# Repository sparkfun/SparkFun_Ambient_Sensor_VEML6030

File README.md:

SparkFun Ambient Light Sensor VEML6030 (Qwiic) 
========================================

[*SparkFun Ambient LIght Sensor - VEML6030 (Qwiic) (SEN-15436)*](https://www.sparkfun.com/products/15436)

The SparkFun Ambient Light Sensor - VEML6030 (Qwiic) is an I<sup>2</sup>C enabled
ambient light sensor with high sensitivity and high accuracy. It reads ambient
light in Lux and boasts a number of nice features including: the ability to set
high and low thresholds for an optional interrupt, power saving features that enable
single digit micro-amp current draw, and a readable  range from zero to 120,000 Lux. We've also written an Arduino 
library that gives full access to all features and includes example code demonstrating all its' abilities (see link below under **Documentation**). 

Repository Contents
-------------------

* **/Documentation** - Data sheets, additional product information
* **/Hardware** - Eagle design files (.brd, .sch)
* **/Libraries** - Libraries for use with the SparkFun Ambient Light Sensor.
* **/Production** - Production panel files (.brd)

Documentation
--------------
* **[SparkFun Ambient Light Sensor Arduino Library](https://github.com/sparkfun/SparkFun_Ambient_Light_Sensor_Arduino_Library)** - Arduino Library
* **[Hookup Guide](https://learn.sparkfun.com/tutorials/qwiic-ambient-light-sensor-veml6030-hookup-guide)** - Basic hookup guide for the SparkFun Ambient Light Sensor
* **[Qwiic Ecosystem](https://www.sparkfun.com/qwiic)** - Qwiic enabled for fast prototyping!

License Information
-------------------

This product is _**open source**_! 

Please review the LICENSE.md file for license information. 

If you have any questions or concerns on licensing, please contact technical support on our [SparkFun forums](https://forum.sparkfun.com/viewforum.php?f=152).

Distributed as-is; no warranty is given.

- Your friends at SparkFun.

_<COLLABORATION CREDIT>_

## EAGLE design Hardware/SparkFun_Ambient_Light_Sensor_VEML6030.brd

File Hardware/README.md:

SparkFun Ambient Light Sensor VEML6030 Design Files
=====================================

The .sch and .brd files hare are Eagle CAD schematic and PCB design files from SparkFun Electronics.
A freeware version of Eagle can be found [here](http://www.cadsoftusa.com/download-eagle/freeware/).

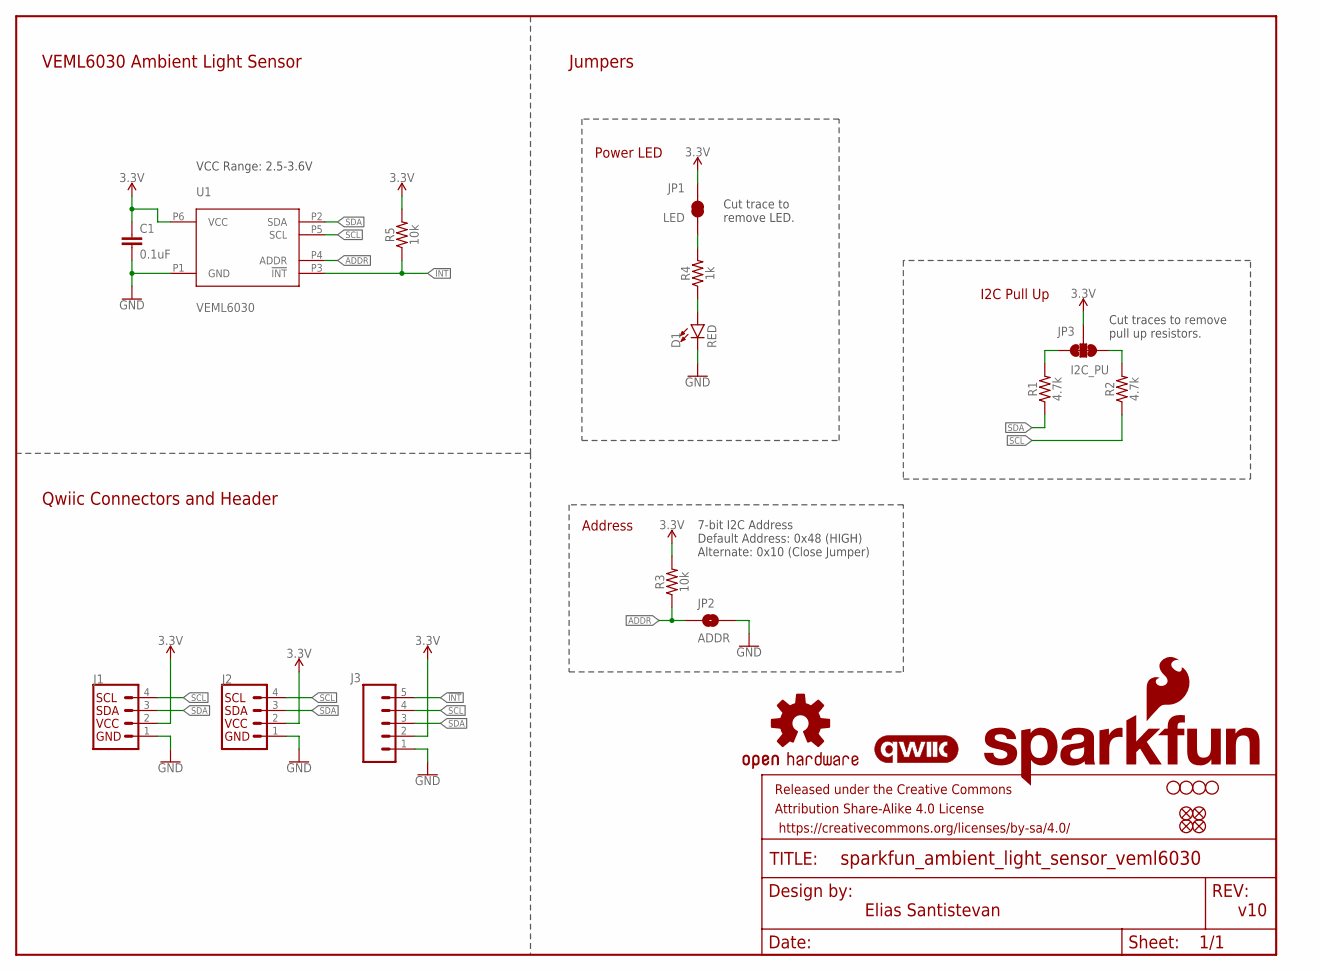
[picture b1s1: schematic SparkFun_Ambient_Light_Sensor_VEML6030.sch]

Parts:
C1: 0.1uF; 0603
D1: RED; LED-0603
FD1, FD2, FD3, FD4: FIDUCIAL1X2; FIDUCIAL-1X2
FRAME1: FRAME-LETTER; CREATIVE_COMMONS
H1, H2, H3, H4: STAND-OFFTIGHT; STAND-OFF-TIGHT
J1, J2: QWIIC_CONNECTORJS-1MM; JST04_1MM_RA
J3: CONN_05NO_SILK; 1X05_NO_SILK
JP1: LED; SMT-JUMPER_2_NC_TRACE_SILK
JP2: ADDR; SMT-JUMPER_2_NO_SILK
JP3: I2C_PU; SMT-JUMPER_3_2-NC_TRACE_SILK
LOGO1: SFE_LOGO_NAME_FLAME.1_INCH; SFE_LOGO_NAME_FLAME_.1
LOGO2: OSHW-LOGOS; OSHW-LOGO-S
R1, R2: 4.7k; 0603
R3, R5: 10k; 0603
R4: 1k; 0603
U1: VEML6030
U$1: QWIIC_LOGO_5MM; QWIIC_5MM

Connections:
3.3V: C1.1, J1.2, J2.2, J3.2, JP1.2, JP3.2, R3.2, R5.2, U1.P6 (VCC)
!INT: J3.5, R5.1, U1.P3 (!INT)
ADDR: JP2.1, R3.1, U1.P4 (ADDR)
GND: C1.2, D1.C, J1.1, J2.1, J3.1, JP2.2, U1.P1 (GND)
unnamed: D1.A, R4.1
unnamed: JP1.1, R4.2
unnamed: JP3.3, R1.2
unnamed: JP3.1, R2.2
SCL: J1.4, J2.4, J3.4, R2.1, U1.P5 (SCL)
SDA: J1.3, J2.3, J3.3, R1.1, U1.P2 (SDA)

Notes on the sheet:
v10
Elias Santistevan
Qwiic Connectors and Header
VEML6030 Ambient Light Sensor
Jumpers
Power LED
I2C Pull Up
Address
7-bit I2C Address Default Address: 0x48 (HIGH) Alternate: 0x10 (Close Jumper)
Cut trace to remove LED.
Cut traces to remove pull up resistors.
VCC Range: 2.5-3.6V

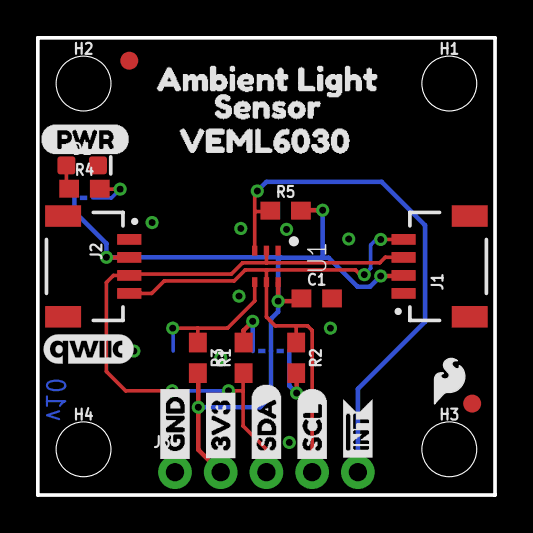
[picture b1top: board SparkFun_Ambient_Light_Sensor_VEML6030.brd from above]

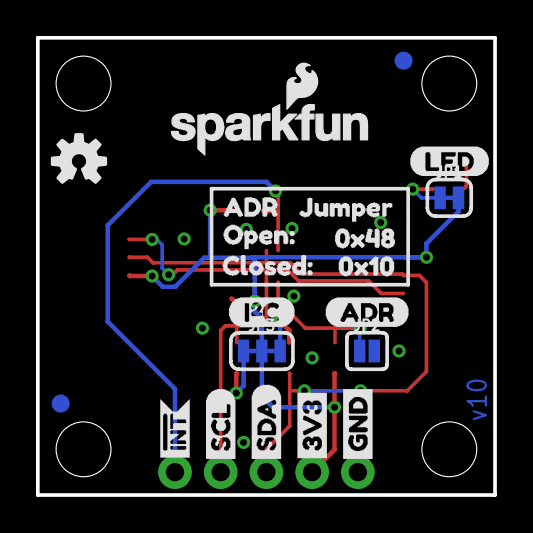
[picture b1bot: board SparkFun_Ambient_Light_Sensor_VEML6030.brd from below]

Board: 2 copper layers, 25.4 x 25.4 mm, 50 parts (21 on the bottom side), 10 nets.

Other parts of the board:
U$2, U$11: 3V3-04
U$3, U$8: GND-04
U$4, U$9: SDA-[)
U$5, U$10: SCL-[)
U$6, U$7: INT#-[<
U$12: I_SUPER2_C-()-04
U$13: ADR-()
U$14: LED0
U$15: AMBIENT_LIGHT0
U$16: SENSOR1
U$17: VEML60302
U$18: SFE_LOGO_FLAME_.1
U$19: PWR-()-04
U$20: CLOSED#2
U$21: OPEN#0
U$22: 0X481
U$24: 0X103
U$25: ADR0
U$26: JUMPER1

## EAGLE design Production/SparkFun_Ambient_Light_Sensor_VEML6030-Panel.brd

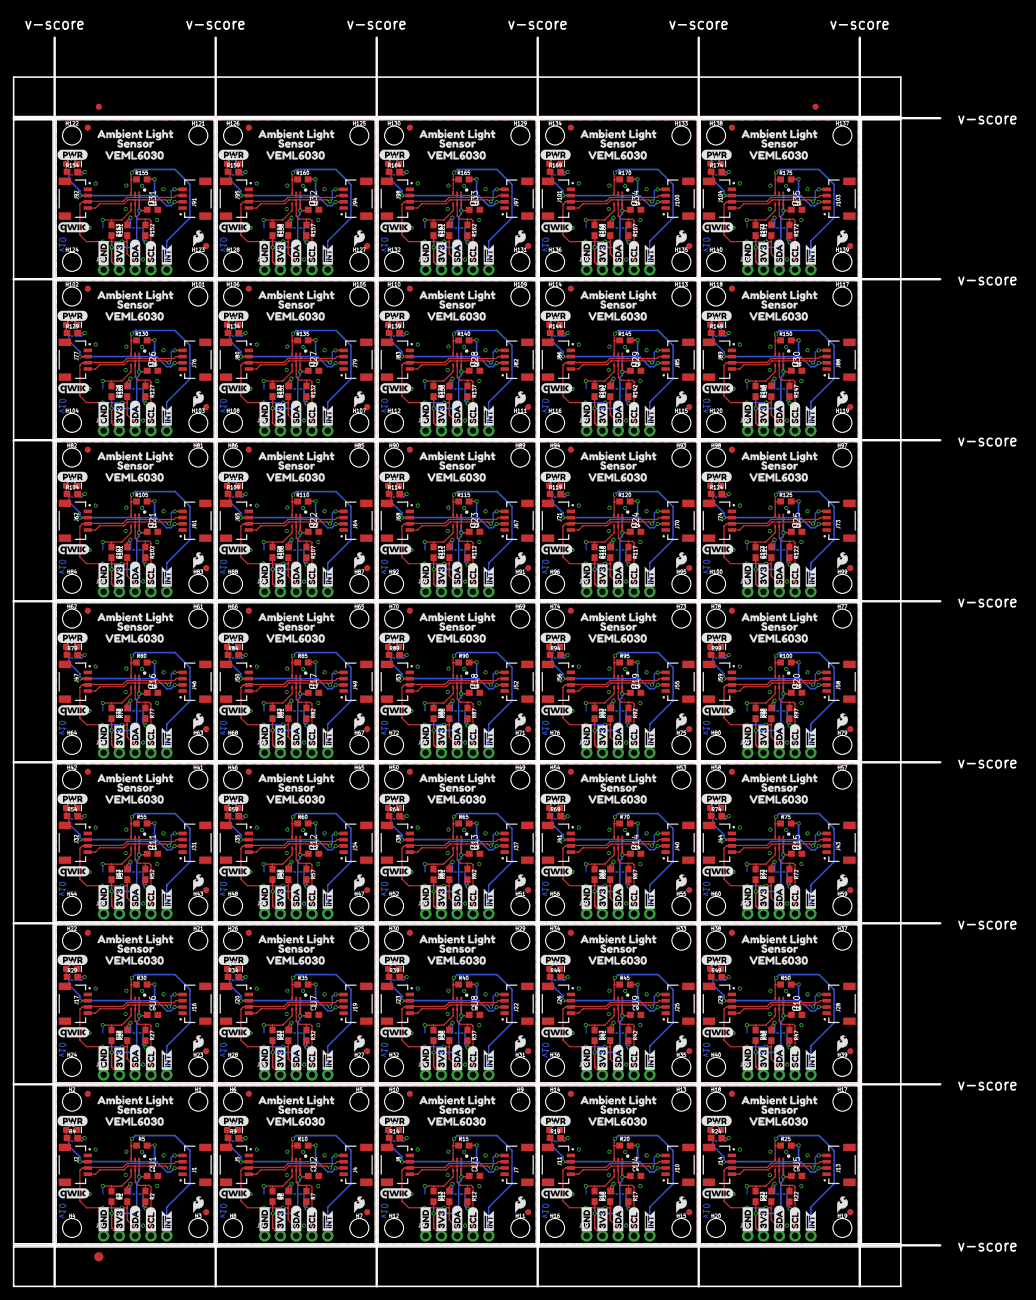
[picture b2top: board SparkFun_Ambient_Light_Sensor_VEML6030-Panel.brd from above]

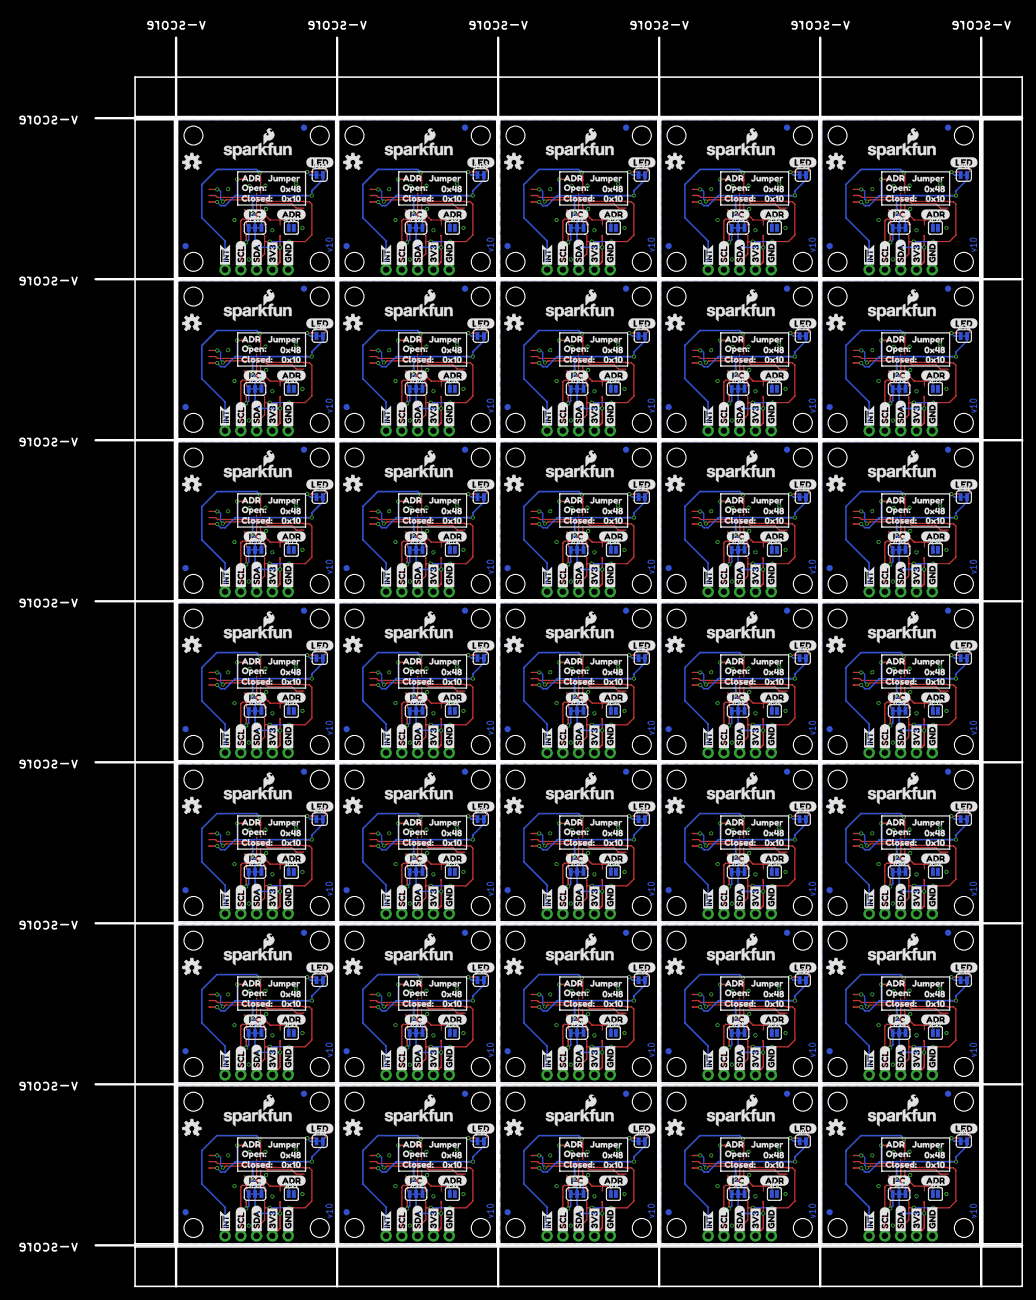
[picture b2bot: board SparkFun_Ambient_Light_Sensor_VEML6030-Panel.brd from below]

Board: 2 copper layers, 149.1 x 200.9 mm, 1718 parts (735 on the bottom side), 350 nets.

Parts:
C1, C2, C3, C4, C5, C6, C7, C8, C9, C10, C11, C12, C13, C14, C15, C16, C17, C18, C19, C20, C21, C22, C23, C24, C25, C26, C27, C28, C29, C30, C31, C32, C33, C34, C35: 0.1uF; 0603
D1, D2, D3, D4, D5, D6, D7, D8, D9, D10, D11, D12, D13, D14, D15, D16, D17, D18, D19, D20, D21, D22, D23, D24, D25, D26, D27, D28, D29, D30, D31, D32, D33, D34, D35: RED; LED-0603
E$1, E$2: FIDUCIAL-1X2
E$3: FIDUCIAL-1.5X3
FD1, FD2, FD3, FD4, FD5, FD6, FD7, FD8, FD9, FD10, FD11, FD12, FD13, FD14, FD15, FD16, FD17, FD18, FD19, FD20, FD21, FD22, FD23, FD24, FD25, FD26, FD27, FD28, FD29, FD30, FD31, FD32, FD33, FD34, FD35, FD36, FD37, FD38, FD39, FD40, FD41, FD42, FD43, FD44, FD45, FD46, FD47, FD48, FD49, FD50, FD51, FD52, FD53, FD54, FD55, FD56, FD57, FD58, FD59, FD60, FD61, FD62, FD63, FD64, FD65, FD66, FD67, FD68, FD69, FD70, FD71, FD72, FD73, FD74, FD75, FD76, FD77, FD78, FD79, FD80, FD81, FD82, FD83, FD84, FD85, FD86, FD87, FD88, FD89, FD90, FD91, FD92, FD93, FD94, FD95, FD96, FD97, FD98, FD99, FD100, FD101, FD102, FD103, FD104, FD105, FD106, FD107, FD108, FD109, FD110, FD111, FD112, FD113, FD114, FD115, FD116, FD117, FD118, FD119, FD120, FD121, FD122, FD123, FD124, FD125, FD126, FD127, FD128, FD129, FD130, FD131, FD132, FD133, FD134, FD135, FD136, FD137, FD138, FD139, FD140: FIDUCIAL1X2; FIDUCIAL-1X2
H1, H2, H3, H4, H5, H6, H7, H8, H9, H10, H11, H12, H13, H14, H15, H16, H17, H18, H19, H20, H21, H22, H23, H24, H25, H26, H27, H28, H29, H30, H31, H32, H33, H34, H35, H36, H37, H38, H39, H40, H41, H42, H43, H44, H45, H46, H47, H48, H49, H50, H51, H52, H53, H54, H55, H56, H57, H58, H59, H60, H61, H62, H63, H64, H65, H66, H67, H68, H69, H70, H71, H72, H73, H74, H75, H76, H77, H78, H79, H80, H81, H82, H83, H84, H85, H86, H87, H88, H89, H90, H91, H92, H93, H94, H95, H96, H97, H98, H99, H100, H101, H102, H103, H104, H105, H106, H107, H108, H109, H110, H111, H112, H113, H114, H115, H116, H117, H118, H119, H120, H121, H122, H123, H124, H125, H126, H127, H128, H129, H130, H131, H132, H133, H134, H135, H136, H137, H138, H139, H140: STAND-OFFTIGHT; STAND-OFF-TIGHT
J1, J2, J4, J5, J7, J8, J10, J11, J13, J14, J16, J17, J19, J20, J22, J23, J25, J26, J28, J29, J31, J32, J34, J35, J37, J38, J40, J41, J43, J44, J46, J47, J49, J50, J52, J53, J55, J56, J58, J59, J61, J62, J64, J65, J67, J68, J70, J71, J73, J74, J76, J77, J79, J80, J82, J83, J85, J86, J88, J89, J91, J92, J94, J95, J97, J98, J100, J101, J103, J104: JST04_1MM_RA
J3, J6, J9, J12, J15, J18, J21, J24, J27, J30, J33, J36, J39, J42, J45, J48, J51, J54, J57, J60, J63, J66, J69, J72, J75, J78, J81, J84, J87, J90, J93, J96, J99, J102, J105: 1X05_NO_SILK
JP1, JP4, JP7, JP10, JP13, JP16, JP19, JP22, JP25, JP28, JP31, JP34, JP37, JP40, JP43, JP46, JP49, JP52, JP55, JP58, JP61, JP64, JP67, JP70, JP73, JP76, JP79, JP82, JP85, JP88, JP91, JP94, JP97, JP100, JP103: LED; SMT-JUMPER_2_NC_TRACE_SILK
JP2, JP5, JP8, JP11, JP14, JP17, JP20, JP23, JP26, JP29, JP32, JP35, JP38, JP41, JP44, JP47, JP50, JP53, JP56, JP59, JP62, JP65, JP68, JP71, JP74, JP77, JP80, JP83, JP86, JP89, JP92, JP95, JP98, JP101, JP104: ADDR; SMT-JUMPER_2_NO_SILK
JP3, JP6, JP9, JP12, JP15, JP18, JP21, JP24, JP27, JP30, JP33, JP36, JP39, JP42, JP45, JP48, JP51, JP54, JP57, JP60, JP63, JP66, JP69, JP72, JP75, JP78, JP81, JP84, JP87, JP90, JP93, JP96, JP99, JP102, JP105: I2C_PU; SMT-JUMPER_3_2-NC_TRACE_SILK
LOGO1, LOGO3, LOGO5, LOGO7, LOGO9, LOGO11, LOGO13, LOGO15, LOGO17, LOGO19, LOGO21, LOGO23, LOGO25, LOGO27, LOGO29, LOGO31, LOGO33, LOGO35, LOGO37, LOGO39, LOGO41, LOGO43, LOGO45, LOGO47, LOGO49, LOGO51, LOGO53, LOGO55, LOGO57, LOGO59, LOGO61, LOGO63, LOGO65, LOGO67, LOGO69: SFE_LOGO_NAME_FLAME.1_INCH; SFE_LOGO_NAME_FLAME_.1
LOGO2, LOGO4, LOGO6, LOGO8, LOGO10, LOGO12, LOGO14, LOGO16, LOGO18, LOGO20, LOGO22, LOGO24, LOGO26, LOGO28, LOGO30, LOGO32, LOGO34, LOGO36, LOGO38, LOGO40, LOGO42, LOGO44, LOGO46, LOGO48, LOGO50, LOGO52, LOGO54, LOGO56, LOGO58, LOGO60, LOGO62, LOGO64, LOGO66, LOGO68, LOGO70: OSHW-LOGOS; OSHW-LOGO-S
R1, R2, R6, R7, R11, R12, R16, R17, R21, R22, R26, R27, R31, R32, R36, R37, R41, R42, R46, R47, R51, R52, R56, R57, R61, R62, R66, R67, R71, R72, R76, R77, R81, R82, R86, R87, R91, R92, R96, R97, R101, R102, R106, R107, R111, R112, R116, R117, R121, R122, R126, R127, R131, R132, R136, R137, R141, R142, R146, R147, R151, R152, R156, R157, R161, R162, R166, R167, R171, R172: 4.7k; 0603
R3, R5, R8, R10, R13, R15, R18, R20, R23, R25, R28, R30, R33, R35, R38, R40, R43, R45, R48, R50, R53, R55, R58, R60, R63, R65, R68, R70, R73, R75, R78, R80, R83, R85, R88, R90, R93, R95, R98, R100, R103, R105, R108, R110, R113, R115, R118, R120, R123, R125, R128, R130, R133, R135, R138, R140, R143, R145, R148, R150, R153, R155, R158, R160, R163, R165, R168, R170, R173, R175: 10k; 0603
R4, R9, R14, R19, R24, R29, R34, R39, R44, R49, R54, R59, R64, R69, R74, R79, R84, R89, R94, R99, R104, R109, R114, R119, R124, R129, R134, R139, R144, R149, R154, R159, R164, R169, R174: 1k; 0603
U1, U2, U3, U4, U5, U6, U7, U8, U9, U10, U11, U12, U13, U14, U15, U16, U17, U18, U19, U20, U21, U22, U23, U24, U25, U26, U27, U28, U29, U30, U31, U32, U33, U34, U35: VEML6030
U$1, U$23, U$51, U$76, U$101, U$126, U$151, U$176, U$201, U$226, U$251, U$276, U$301, U$326, U$351, U$376, U$401, U$426, U$451, U$476, U$501, U$526, U$551, U$576, U$601, U$626, U$651, U$676, U$701, U$726, U$751, U$776, U$801, U$826, U$851: QWIIC_LOGO_5MM; QWIIC_5MM
U$2, U$11, U$27, U$36, U$52, U$61, U$77, U$86, U$102, U$111, U$127, U$136, U$152, U$161, U$177, U$186, U$202, U$211, U$227, U$236, U$252, U$261, U$277, U$286, U$302, U$311, U$327, U$336, U$352, U$361, U$377, U$386, U$402, U$411, U$427, U$436, U$452, U$461, U$477, U$486, U$502, U$511, U$527, U$536, U$552, U$561, U$577, U$586, U$602, U$611, U$627, U$636, U$652, U$661, U$677, U$686, U$702, U$711, U$727, U$736, U$752, U$761, U$777, U$786, U$802, U$811, U$827, U$836, U$852, U$861: 3V3-04
U$3, U$8, U$28, U$33, U$53, U$58, U$78, U$83, U$103, U$108, U$128, U$133, U$153, U$158, U$178, U$183, U$203, U$208, U$228, U$233, U$253, U$258, U$278, U$283, U$303, U$308, U$328, U$333, U$353, U$358, U$378, U$383, U$403, U$408, U$428, U$433, U$453, U$458, U$478, U$483, U$503, U$508, U$528, U$533, U$553, U$558, U$578, U$583, U$603, U$608, U$628, U$633, U$653, U$658, U$678, U$683, U$703, U$708, U$728, U$733, U$753, U$758, U$778, U$783, U$803, U$808, U$828, U$833, U$853, U$858: GND-04
U$4, U$9, U$29, U$34, U$54, U$59, U$79, U$84, U$104, U$109, U$129, U$134, U$154, U$159, U$179, U$184, U$204, U$209, U$229, U$234, U$254, U$259, U$279, U$284, U$304, U$309, U$329, U$334, U$354, U$359, U$379, U$384, U$404, U$409, U$429, U$434, U$454, U$459, U$479, U$484, U$504, U$509, U$529, U$534, U$554, U$559, U$579, U$584, U$604, U$609, U$629, U$634, U$654, U$659, U$679, U$684, U$704, U$709, U$729, U$734, U$754, U$759, U$779, U$784, U$804, U$809, U$829, U$834, U$854, U$859: SDA-[)
U$5, U$10, U$30, U$35, U$55, U$60, U$80, U$85, U$105, U$110, U$130, U$135, U$155, U$160, U$180, U$185, U$205, U$210, U$230, U$235, U$255, U$260, U$280, U$285, U$305, U$310, U$330, U$335, U$355, U$360, U$380, U$385, U$405, U$410, U$430, U$435, U$455, U$460, U$480, U$485, U$505, U$510, U$530, U$535, U$555, U$560, U$580, U$585, U$605, U$610, U$630, U$635, U$655, U$660, U$680, U$685, U$705, U$710, U$730, U$735, U$755, U$760, U$780, U$785, U$805, U$810, U$830, U$835, U$855, U$860: SCL-[)
U$6, U$7, U$31, U$32, U$56, U$57, U$81, U$82, U$106, U$107, U$131, U$132, U$156, U$157, U$181, U$182, U$206, U$207, U$231, U$232, U$256, U$257, U$281, U$282, U$306, U$307, U$331, U$332, U$356, U$357, U$381, U$382, U$406, U$407, U$431, U$432, U$456, U$457, U$481, U$482, U$506, U$507, U$531, U$532, U$556, U$557, U$581, U$582, U$606, U$607, U$631, U$632, U$656, U$657, U$681, U$682, U$706, U$707, U$731, U$732, U$756, U$757, U$781, U$782, U$806, U$807, U$831, U$832, U$856, U$857: INT#-[<
U$12, U$37, U$62, U$87, U$112, U$137, U$162, U$187, U$212, U$237, U$262, U$287, U$312, U$337, U$362, U$387, U$412, U$437, U$462, U$487, U$512, U$537, U$562, U$587, U$612, U$637, U$662, U$687, U$712, U$737, U$762, U$787, U$812, U$837, U$862: I_SUPER2_C-()-04
U$13, U$38, U$63, U$88, U$113, U$138, U$163, U$188, U$213, U$238, U$263, U$288, U$313, U$338, U$363, U$388, U$413, U$438, U$463, U$488, U$513, U$538, U$563, U$588, U$613, U$638, U$663, U$688, U$713, U$738, U$763, U$788, U$813, U$838, U$863: ADR-()
U$14, U$39, U$64, U$89, U$114, U$139, U$164, U$189, U$214, U$239, U$264, U$289, U$314, U$339, U$364, U$389, U$414, U$439, U$464, U$489, U$514, U$539, U$564, U$589, U$614, U$639, U$664, U$689, U$714, U$739, U$764, U$789, U$814, U$839, U$864: LED0
U$15, U$40, U$65, U$90, U$115, U$140, U$165, U$190, U$215, U$240, U$265, U$290, U$315, U$340, U$365, U$390, U$415, U$440, U$465, U$490, U$515, U$540, U$565, U$590, U$615, U$640, U$665, U$690, U$715, U$740, U$765, U$790, U$815, U$840, U$865: AMBIENT_LIGHT0
U$16, U$41, U$66, U$91, U$116, U$141, U$166, U$191, U$216, U$241, U$266, U$291, U$316, U$341, U$366, U$391, U$416, U$441, U$466, U$491, U$516, U$541, U$566, U$591, U$616, U$641, U$666, U$691, U$716, U$741, U$766, U$791, U$816, U$841, U$866: SENSOR1
U$17, U$42, U$67, U$92, U$117, U$142, U$167, U$192, U$217, U$242, U$267, U$292, U$317, U$342, U$367, U$392, U$417, U$442, U$467, U$492, U$517, U$542, U$567, U$592, U$617, U$642, U$667, U$692, U$717, U$742, U$767, U$792, U$817, U$842, U$867: VEML60302
U$18, U$43, U$68, U$93, U$118, U$143, U$168, U$193, U$218, U$243, U$268, U$293, U$318, U$343, U$368, U$393, U$418, U$443, U$468, U$493, U$518, U$543, U$568, U$593, U$618, U$643, U$668, U$693, U$718, U$743, U$768, U$793, U$818, U$843, U$868: SFE_LOGO_FLAME_.1
U$19, U$44, U$69, U$94, U$119, U$144, U$169, U$194, U$219, U$244, U$269, U$294, U$319, U$344, U$369, U$394, U$419, U$444, U$469, U$494, U$519, U$544, U$569, U$594, U$619, U$644, U$669, U$694, U$719, U$744, U$769, U$794, U$819, U$844, U$869: PWR-()-04
U$20, U$49, U$74, U$99, U$124, U$149, U$174, U$199, U$224, U$249, U$274, U$299, U$324, U$349, U$374, U$399, U$424, U$449, U$474, U$499, U$524, U$549, U$574, U$599, U$624, U$649, U$674, U$699, U$724, U$749, U$774, U$799, U$824, U$849, U$874: CLOSED#2
U$21, U$50, U$75, U$100, U$125, U$150, U$175, U$200, U$225, U$250, U$275, U$300, U$325, U$350, U$375, U$400, U$425, U$450, U$475, U$500, U$525, U$550, U$575, U$600, U$625, U$650, U$675, U$700, U$725, U$750, U$775, U$800, U$825, U$850, U$875: OPEN#0
U$22, U$45, U$70, U$95, U$120, U$145, U$170, U$195, U$220, U$245, U$270, U$295, U$320, U$345, U$370, U$395, U$420, U$445, U$470, U$495, U$520, U$545, U$570, U$595, U$620, U$645, U$670, U$695, U$720, U$745, U$770, U$795, U$820, U$845, U$870: 0X481
U$24, U$46, U$71, U$96, U$121, U$146, U$171, U$196, U$221, U$246, U$271, U$296, U$321, U$346, U$371, U$396, U$421, U$446, U$471, U$496, U$521, U$546, U$571, U$596, U$621, U$646, U$671, U$696, U$721, U$746, U$771, U$796, U$821, U$846, U$871: 0X103
U$25, U$47, U$72, U$97, U$122, U$147, U$172, U$197, U$222, U$247, U$272, U$297, U$322, U$347, U$372, U$397, U$422, U$447, U$472, U$497, U$522, U$547, U$572, U$597, U$622, U$647, U$672, U$697, U$722, U$747, U$772, U$797, U$822, U$847, U$872: ADR0
U$26, U$48, U$73, U$98, U$123, U$148, U$173, U$198, U$223, U$248, U$273, U$298, U$323, U$348, U$373, U$398, U$423, U$448, U$473, U$498, U$523, U$548, U$573, U$598, U$623, U$648, U$673, U$698, U$723, U$748, U$773, U$798, U$823, U$848, U$873: JUMPER1

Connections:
3.3V: C1.1, J1.2, J2.2, J3.2, JP1.2, JP3.2, R3.2, R5.2, U1.P6
3.3V1: C2.1, J4.2, J5.2, J6.2, JP4.2, JP6.2, R8.2, R10.2, U2.P6
3.3V2: C3.1, J7.2, J8.2, J9.2, JP7.2, JP9.2, R13.2, R15.2, U3.P6
3.3V3: C4.1, J10.2, J11.2, J12.2, JP10.2, JP12.2, R18.2, R20.2, U4.P6
3.3V4: C5.1, J13.2, J14.2, J15.2, JP13.2, JP15.2, R23.2, R25.2, U5.P6
3.3V5: C6.1, J16.2, J17.2, J18.2, JP16.2, JP18.2, R28.2, R30.2, U6.P6
3.3V6: C7.1, J19.2, J20.2, J21.2, JP19.2, JP21.2, R33.2, R35.2, U7.P6
3.3V7: C8.1, J22.2, J23.2, J24.2, JP22.2, JP24.2, R38.2, R40.2, U8.P6
3.3V8: C9.1, J25.2, J26.2, J27.2, JP25.2, JP27.2, R43.2, R45.2, U9.P6
3.3V9: C10.1, J28.2, J29.2, J30.2, JP28.2, JP30.2, R48.2, R50.2, U10.P6
3.3V10: C11.1, J31.2, J32.2, J33.2, JP31.2, JP33.2, R53.2, R55.2, U11.P6
3.3V11: C12.1, J34.2, J35.2, J36.2, JP34.2, JP36.2, R58.2, R60.2, U12.P6
3.3V12: C13.1, J37.2, J38.2, J39.2, JP37.2, JP39.2, R63.2, R65.2, U13.P6
3.3V13: C14.1, J40.2, J41.2, J42.2, JP40.2, JP42.2, R68.2, R70.2, U14.P6
3.3V14: C15.1, J43.2, J44.2, J45.2, JP43.2, JP45.2, R73.2, R75.2, U15.P6
3.3V15: C16.1, J46.2, J47.2, J48.2, JP46.2, JP48.2, R78.2, R80.2, U16.P6
3.3V16: C17.1, J49.2, J50.2, J51.2, JP49.2, JP51.2, R83.2, R85.2, U17.P6
3.3V17: C18.1, J52.2, J53.2, J54.2, JP52.2, JP54.2, R88.2, R90.2, U18.P6
3.3V18: C19.1, J55.2, J56.2, J57.2, JP55.2, JP57.2, R93.2, R95.2, U19.P6
3.3V19: C20.1, J58.2, J59.2, J60.2, JP58.2, JP60.2, R98.2, R100.2, U20.P6
3.3V20: C21.1, J61.2, J62.2, J63.2, JP61.2, JP63.2, R103.2, R105.2, U21.P6
3.3V21: C22.1, J64.2, J65.2, J66.2, JP64.2, JP66.2, R108.2, R110.2, U22.P6
3.3V22: C23.1, J67.2, J68.2, J69.2, JP67.2, JP69.2, R113.2, R115.2, U23.P6
3.3V23: C24.1, J70.2, J71.2, J72.2, JP70.2, JP72.2, R118.2, R120.2, U24.P6
3.3V24: C25.1, J73.2, J74.2, J75.2, JP73.2, JP75.2, R123.2, R125.2, U25.P6
3.3V25: C26.1, J76.2, J77.2, J78.2, JP76.2, JP78.2, R128.2, R130.2, U26.P6
3.3V26: C27.1, J79.2, J80.2, J81.2, JP79.2, JP81.2, R133.2, R135.2, U27.P6
3.3V27: C28.1, J82.2, J83.2, J84.2, JP82.2, JP84.2, R138.2, R140.2, U28.P6
3.3V28: C29.1, J85.2, J86.2, J87.2, JP85.2, JP87.2, R143.2, R145.2, U29.P6
3.3V29: C30.1, J88.2, J89.2, J90.2, JP88.2, JP90.2, R148.2, R150.2, U30.P6
3.3V30: C31.1, J91.2, J92.2, J93.2, JP91.2, JP93.2, R153.2, R155.2, U31.P6
3.3V31: C32.1, J94.2, J95.2, J96.2, JP94.2, JP96.2, R158.2, R160.2, U32.P6
3.3V32: C33.1, J97.2, J98.2, J99.2, JP97.2, JP99.2, R163.2, R165.2, U33.P6
3.3V33: C34.1, J100.2, J101.2, J102.2, JP100.2, JP102.2, R168.2, R170.2, U34.P6
3.3V34: C35.1, J103.2, J104.2, J105.2, JP103.2, JP105.2, R173.2, R175.2, U35.P6
!INT: J3.5, R5.1, U1.P3
!INT1: J6.5, R10.1, U2.P3
!INT2: J9.5, R15.1, U3.P3
!INT3: J12.5, R20.1, U4.P3
!INT4: J15.5, R25.1, U5.P3
!INT5: J18.5, R30.1, U6.P3
!INT6: J21.5, R35.1, U7.P3
!INT7: J24.5, R40.1, U8.P3
!INT8: J27.5, R45.1, U9.P3
!INT9: J30.5, R50.1, U10.P3
!INT10: J33.5, R55.1, U11.P3
!INT11: J36.5, R60.1, U12.P3
!INT12: J39.5, R65.1, U13.P3
!INT13: J42.5, R70.1, U14.P3
!INT14: J45.5, R75.1, U15.P3
!INT15: J48.5, R80.1, U16.P3
!INT16: J51.5, R85.1, U17.P3
!INT17: J54.5, R90.1, U18.P3
!INT18: J57.5, R95.1, U19.P3
!INT19: J60.5, R100.1, U20.P3
!INT20: J63.5, R105.1, U21.P3
!INT21: J66.5, R110.1, U22.P3
!INT22: J69.5, R115.1, U23.P3
!INT23: J72.5, R120.1, U24.P3
!INT24: J75.5, R125.1, U25.P3
!INT25: J78.5, R130.1, U26.P3
!INT26: J81.5, R135.1, U27.P3
!INT27: J84.5, R140.1, U28.P3
!INT28: J87.5, R145.1, U29.P3
!INT29: J90.5, R150.1, U30.P3
!INT30: J93.5, R155.1, U31.P3
!INT31: J96.5, R160.1, U32.P3
!INT32: J99.5, R165.1, U33.P3
!INT33: J102.5, R170.1, U34.P3
!INT34: J105.5, R175.1, U35.P3
ADDR: JP2.1, R3.1, U1.P4
ADDR1: JP5.1, R8.1, U2.P4
ADDR2: JP8.1, R13.1, U3.P4
ADDR3: JP11.1, R18.1, U4.P4
ADDR4: JP14.1, R23.1, U5.P4
ADDR5: JP17.1, R28.1, U6.P4
ADDR6: JP20.1, R33.1, U7.P4
ADDR7: JP23.1, R38.1, U8.P4
ADDR8: JP26.1, R43.1, U9.P4
ADDR9: JP29.1, R48.1, U10.P4
ADDR10: JP32.1, R53.1, U11.P4
ADDR11: JP35.1, R58.1, U12.P4
ADDR12: JP38.1, R63.1, U13.P4
ADDR13: JP41.1, R68.1, U14.P4
ADDR14: JP44.1, R73.1, U15.P4
ADDR15: JP47.1, R78.1, U16.P4
ADDR16: JP50.1, R83.1, U17.P4
ADDR17: JP53.1, R88.1, U18.P4
ADDR18: JP56.1, R93.1, U19.P4
ADDR19: JP59.1, R98.1, U20.P4
ADDR20: JP62.1, R103.1, U21.P4
ADDR21: JP65.1, R108.1, U22.P4
ADDR22: JP68.1, R113.1, U23.P4
ADDR23: JP71.1, R118.1, U24.P4
ADDR24: JP74.1, R123.1, U25.P4
ADDR25: JP77.1, R128.1, U26.P4
ADDR26: JP80.1, R133.1, U27.P4
ADDR27: JP83.1, R138.1, U28.P4
ADDR28: JP86.1, R143.1, U29.P4
ADDR29: JP89.1, R148.1, U30.P4
ADDR30: JP92.1, R153.1, U31.P4
ADDR31: JP95.1, R158.1, U32.P4
ADDR32: JP98.1, R163.1, U33.P4
ADDR33: JP101.1, R168.1, U34.P4
ADDR34: JP104.1, R173.1, U35.P4
GND: C1.2, D1.C, J1.1, J2.1, J3.1, JP2.2, U1.P1
GND1: C2.2, D2.C, J4.1, J5.1, J6.1, JP5.2, U2.P1
GND2: C3.2, D3.C, J7.1, J8.1, J9.1, JP8.2, U3.P1
GND3: C4.2, D4.C, J10.1, J11.1, J12.1, JP11.2, U4.P1
GND4: C5.2, D5.C, J13.1, J14.1, J15.1, JP14.2, U5.P1
GND5: C6.2, D6.C, J16.1, J17.1, J18.1, JP17.2, U6.P1
GND6: C7.2, D7.C, J19.1, J20.1, J21.1, JP20.2, U7.P1
GND7: C8.2, D8.C, J22.1, J23.1, J24.1, JP23.2, U8.P1
GND8: C9.2, D9.C, J25.1, J26.1, J27.1, JP26.2, U9.P1
GND9: C10.2, D10.C, J28.1, J29.1, J30.1, JP29.2, U10.P1
GND10: C11.2, D11.C, J31.1, J32.1, J33.1, JP32.2, U11.P1
GND11: C12.2, D12.C, J34.1, J35.1, J36.1, JP35.2, U12.P1
GND12: C13.2, D13.C, J37.1, J38.1, J39.1, JP38.2, U13.P1
GND13: C14.2, D14.C, J40.1, J41.1, J42.1, JP41.2, U14.P1
GND14: C15.2, D15.C, J43.1, J44.1, J45.1, JP44.2, U15.P1
GND15: C16.2, D16.C, J46.1, J47.1, J48.1, JP47.2, U16.P1
GND16: C17.2, D17.C, J49.1, J50.1, J51.1, JP50.2, U17.P1
GND17: C18.2, D18.C, J52.1, J53.1, J54.1, JP53.2, U18.P1
GND18: C19.2, D19.C, J55.1, J56.1, J57.1, JP56.2, U19.P1
GND19: C20.2, D20.C, J58.1, J59.1, J60.1, JP59.2, U20.P1
GND20: C21.2, D21.C, J61.1, J62.1, J63.1, JP62.2, U21.P1
GND21: C22.2, D22.C, J64.1, J65.1, J66.1, JP65.2, U22.P1
GND22: C23.2, D23.C, J67.1, J68.1, J69.1, JP68.2, U23.P1
GND23: C24.2, D24.C, J70.1, J71.1, J72.1, JP71.2, U24.P1
GND24: C25.2, D25.C, J73.1, J74.1, J75.1, JP74.2, U25.P1
GND25: C26.2, D26.C, J76.1, J77.1, J78.1, JP77.2, U26.P1
GND26: C27.2, D27.C, J79.1, J80.1, J81.1, JP80.2, U27.P1
GND27: C28.2, D28.C, J82.1, J83.1, J84.1, JP83.2, U28.P1
GND28: C29.2, D29.C, J85.1, J86.1, J87.1, JP86.2, U29.P1
GND29: C30.2, D30.C, J88.1, J89.1, J90.1, JP89.2, U30.P1
GND30: C31.2, D31.C, J91.1, J92.1, J93.1, JP92.2, U31.P1
GND31: C32.2, D32.C, J94.1, J95.1, J96.1, JP95.2, U32.P1
GND32: C33.2, D33.C, J97.1, J98.1, J99.1, JP98.2, U33.P1
GND33: C34.2, D34.C, J100.1, J101.1, J102.1, JP101.2, U34.P1
GND34: C35.2, D35.C, J103.1, J104.1, J105.1, JP104.2, U35.P1
unnamed: D1.A, R4.1
unnamed: JP1.1, R4.2
unnamed: JP3.3, R1.2
unnamed: JP3.1, R2.2
unnamed: D2.A, R9.1
unnamed: JP4.1, R9.2
unnamed: JP6.3, R6.2
unnamed: JP6.1, R7.2
unnamed: D3.A, R14.1
unnamed: JP7.1, R14.2
unnamed: JP9.3, R11.2
unnamed: JP9.1, R12.2
unnamed: D4.A, R19.1
unnamed: JP10.1, R19.2
unnamed: JP12.3, R16.2
unnamed: JP12.1, R17.2
unnamed: D5.A, R24.1
unnamed: JP13.1, R24.2
unnamed: JP15.3, R21.2
unnamed: JP15.1, R22.2
unnamed: D6.A, R29.1
unnamed: JP16.1, R29.2
unnamed: JP18.3, R26.2
unnamed: JP18.1, R27.2
unnamed: D7.A, R34.1
unnamed: JP19.1, R34.2
unnamed: JP21.3, R31.2
unnamed: JP21.1, R32.2
unnamed: D8.A, R39.1
unnamed: JP22.1, R39.2
unnamed: JP24.3, R36.2
unnamed: JP24.1, R37.2
unnamed: D9.A, R44.1
unnamed: JP25.1, R44.2
unnamed: JP27.3, R41.2
unnamed: JP27.1, R42.2
unnamed: D10.A, R49.1
unnamed: JP28.1, R49.2
unnamed: JP30.3, R46.2
unnamed: JP30.1, R47.2
unnamed: D11.A, R54.1
unnamed: JP31.1, R54.2
unnamed: JP33.3, R51.2
unnamed: JP33.1, R52.2
unnamed: D12.A, R59.1
unnamed: JP34.1, R59.2
unnamed: JP36.3, R56.2
unnamed: JP36.1, R57.2
unnamed: D13.A, R64.1
unnamed: JP37.1, R64.2
unnamed: JP39.3, R61.2
unnamed: JP39.1, R62.2
unnamed: D14.A, R69.1
unnamed: JP40.1, R69.2
unnamed: JP42.3, R66.2
unnamed: JP42.1, R67.2
unnamed: D15.A, R74.1
unnamed: JP43.1, R74.2
unnamed: JP45.3, R71.2
unnamed: JP45.1, R72.2
unnamed: D16.A, R79.1
unnamed: JP46.1, R79.2
unnamed: JP48.3, R76.2
unnamed: JP48.1, R77.2
unnamed: D17.A, R84.1
unnamed: JP49.1, R84.2
unnamed: JP51.3, R81.2
unnamed: JP51.1, R82.2
unnamed: D18.A, R89.1
unnamed: JP52.1, R89.2
unnamed: JP54.3, R86.2
unnamed: JP54.1, R87.2
unnamed: D19.A, R94.1
unnamed: JP55.1, R94.2
unnamed: JP57.3, R91.2
unnamed: JP57.1, R92.2
unnamed: D20.A, R99.1
unnamed: JP58.1, R99.2
unnamed: JP60.3, R96.2
unnamed: JP60.1, R97.2
unnamed: D21.A, R104.1
unnamed: JP61.1, R104.2
unnamed: JP63.3, R101.2
unnamed: JP63.1, R102.2
unnamed: D22.A, R109.1
unnamed: JP64.1, R109.2
unnamed: JP66.3, R106.2
unnamed: JP66.1, R107.2
unnamed: D23.A, R114.1
unnamed: JP67.1, R114.2
unnamed: JP69.3, R111.2
unnamed: JP69.1, R112.2
unnamed: D24.A, R119.1
unnamed: JP70.1, R119.2
unnamed: JP72.3, R116.2
unnamed: JP72.1, R117.2
unnamed: D25.A, R124.1
unnamed: JP73.1, R124.2
unnamed: JP75.3, R121.2
unnamed: JP75.1, R122.2
unnamed: D26.A, R129.1
unnamed: JP76.1, R129.2
unnamed: JP78.3, R126.2
unnamed: JP78.1, R127.2
unnamed: D27.A, R134.1
unnamed: JP79.1, R134.2
unnamed: JP81.3, R131.2
unnamed: JP81.1, R132.2
unnamed: D28.A, R139.1
unnamed: JP82.1, R139.2
unnamed: JP84.3, R136.2
unnamed: JP84.1, R137.2
unnamed: D29.A, R144.1
unnamed: JP85.1, R144.2
unnamed: JP87.3, R141.2
unnamed: JP87.1, R142.2
unnamed: D30.A, R149.1
unnamed: JP88.1, R149.2
unnamed: JP90.3, R146.2
unnamed: JP90.1, R147.2
unnamed: D31.A, R154.1
unnamed: JP91.1, R154.2
unnamed: JP93.3, R151.2
unnamed: JP93.1, R152.2
unnamed: D32.A, R159.1
unnamed: JP94.1, R159.2
unnamed: JP96.3, R156.2
unnamed: JP96.1, R157.2
unnamed: D33.A, R164.1
unnamed: JP97.1, R164.2
unnamed: JP99.3, R161.2
unnamed: JP99.1, R162.2
unnamed: D34.A, R169.1
unnamed: JP100.1, R169.2
unnamed: JP102.3, R166.2
unnamed: JP102.1, R167.2
unnamed: D35.A, R174.1
unnamed: JP103.1, R174.2
unnamed: JP105.3, R171.2
unnamed: JP105.1, R172.2
SCL: J1.4, J2.4, J3.4, R2.1, U1.P5
SCL1: J4.4, J5.4, J6.4, R7.1, U2.P5
SCL2: J7.4, J8.4, J9.4, R12.1, U3.P5
SCL3: J10.4, J11.4, J12.4, R17.1, U4.P5
SCL4: J13.4, J14.4, J15.4, R22.1, U5.P5
SCL5: J16.4, J17.4, J18.4, R27.1, U6.P5
SCL6: J19.4, J20.4, J21.4, R32.1, U7.P5
SCL7: J22.4, J23.4, J24.4, R37.1, U8.P5
SCL8: J25.4, J26.4, J27.4, R42.1, U9.P5
SCL9: J28.4, J29.4, J30.4, R47.1, U10.P5
SCL10: J31.4, J32.4, J33.4, R52.1, U11.P5
SCL11: J34.4, J35.4, J36.4, R57.1, U12.P5
SCL12: J37.4, J38.4, J39.4, R62.1, U13.P5
SCL13: J40.4, J41.4, J42.4, R67.1, U14.P5
SCL14: J43.4, J44.4, J45.4, R72.1, U15.P5
SCL15: J46.4, J47.4, J48.4, R77.1, U16.P5
SCL16: J49.4, J50.4, J51.4, R82.1, U17.P5
SCL17: J52.4, J53.4, J54.4, R87.1, U18.P5
SCL18: J55.4, J56.4, J57.4, R92.1, U19.P5
SCL19: J58.4, J59.4, J60.4, R97.1, U20.P5
SCL20: J61.4, J62.4, J63.4, R102.1, U21.P5
SCL21: J64.4, J65.4, J66.4, R107.1, U22.P5
SCL22: J67.4, J68.4, J69.4, R112.1, U23.P5
SCL23: J70.4, J71.4, J72.4, R117.1, U24.P5
SCL24: J73.4, J74.4, J75.4, R122.1, U25.P5
SCL25: J76.4, J77.4, J78.4, R127.1, U26.P5
SCL26: J79.4, J80.4, J81.4, R132.1, U27.P5
SCL27: J82.4, J83.4, J84.4, R137.1, U28.P5
SCL28: J85.4, J86.4, J87.4, R142.1, U29.P5
SCL29: J88.4, J89.4, J90.4, R147.1, U30.P5
SCL30: J91.4, J92.4, J93.4, R152.1, U31.P5
SCL31: J94.4, J95.4, J96.4, R157.1, U32.P5
SCL32: J97.4, J98.4, J99.4, R162.1, U33.P5
SCL33: J100.4, J101.4, J102.4, R167.1, U34.P5
SCL34: J103.4, J104.4, J105.4, R172.1, U35.P5
SDA: J1.3, J2.3, J3.3, R1.1, U1.P2
SDA1: J4.3, J5.3, J6.3, R6.1, U2.P2
SDA2: J7.3, J8.3, J9.3, R11.1, U3.P2
SDA3: J10.3, J11.3, J12.3, R16.1, U4.P2
SDA4: J13.3, J14.3, J15.3, R21.1, U5.P2
SDA5: J16.3, J17.3, J18.3, R26.1, U6.P2
SDA6: J19.3, J20.3, J21.3, R31.1, U7.P2
SDA7: J22.3, J23.3, J24.3, R36.1, U8.P2
SDA8: J25.3, J26.3, J27.3, R41.1, U9.P2
SDA9: J28.3, J29.3, J30.3, R46.1, U10.P2
SDA10: J31.3, J32.3, J33.3, R51.1, U11.P2
SDA11: J34.3, J35.3, J36.3, R56.1, U12.P2
SDA12: J37.3, J38.3, J39.3, R61.1, U13.P2
SDA13: J40.3, J41.3, J42.3, R66.1, U14.P2
SDA14: J43.3, J44.3, J45.3, R71.1, U15.P2
SDA15: J46.3, J47.3, J48.3, R76.1, U16.P2
SDA16: J49.3, J50.3, J51.3, R81.1, U17.P2
SDA17: J52.3, J53.3, J54.3, R86.1, U18.P2
SDA18: J55.3, J56.3, J57.3, R91.1, U19.P2
SDA19: J58.3, J59.3, J60.3, R96.1, U20.P2
SDA20: J61.3, J62.3, J63.3, R101.1, U21.P2
SDA21: J64.3, J65.3, J66.3, R106.1, U22.P2
SDA22: J67.3, J68.3, J69.3, R111.1, U23.P2
SDA23: J70.3, J71.3, J72.3, R116.1, U24.P2
SDA24: J73.3, J74.3, J75.3, R121.1, U25.P2
SDA25: J76.3, J77.3, J78.3, R126.1, U26.P2
SDA26: J79.3, J80.3, J81.3, R131.1, U27.P2
SDA27: J82.3, J83.3, J84.3, R136.1, U28.P2
SDA28: J85.3, J86.3, J87.3, R141.1, U29.P2
SDA29: J88.3, J89.3, J90.3, R146.1, U30.P2
SDA30: J91.3, J92.3, J93.3, R151.1, U31.P2
SDA31: J94.3, J95.3, J96.3, R156.1, U32.P2
SDA32: J97.3, J98.3, J99.3, R161.1, U33.P2
SDA33: J100.3, J101.3, J102.3, R166.1, U34.P2
SDA34: J103.3, J104.3, J105.3, R171.1, U35.P2

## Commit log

2019-06-09 Adds initial commits, still needs:
    *10k pull up on interrupt
    *trace work
    *silk
2019-06-09 Finishes tracework, adds 10k pull up resistor to interrupt pin, needs silk
2019-06-10 Adds silk to board for all things needing lables, adds text to jumpers in schematic,
2019-06-10 Updates polarity marker on VEML6030, adds VCC range to schematic, improves ground pour on the underside.
2019-06-12 Adds application note to documentation, and updates Ambient Light Sensor with SKU
2019-06-12 Routes 3.3V line on underside and data lines on the topside...
    * Adds silk on the underside for address selection
    * Adds power silk to LED
    * moves resistor to top side
    * Fixes GND net on 5 pin header
    * Changes version to v10
2019-06-13 Makes small adjustment to 3.3V traces
2019-06-13 Updates address silk for better clarificaiton, moves 3.3V trace to top near PTH for better ground pour
2019-06-14 Clears up some minor DRC errors, reduces dimension to .008 inches
2019-06-14 Deletes some wire stubs, moves vias that are able to be moved away from silk
2019-06-17 Changed "Default" silk with "Open"
2019-06-17 Centers SparkFun logo on the underside
2019-06-17 Adds production files
2019-06-17 Adds gerbers with paste layer
2019-07-12 Updates Readme
2019-07-12 Removes buzzard labels, updates readme with link to qwiic page, removes other unneccesary readmes
2019-07-12 Fixes gramatically errors in readme
2019-07-12 Adds superscript to I2C
2019-08-19 Updates datasheet.

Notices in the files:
parts and their libraries:
SparkFun-Aesthetics: Licensing: Creative Commons ShareAlike 4.0 International - https://creativecommons.org/licenses/by-sa/4.0
SparkFun-Aesthetics: Released under the Creative Commons Attribution Share-Alike 4.0 License
SparkFun-Aesthetics: https://creativecommons.org/licenses/by-sa/4.0
